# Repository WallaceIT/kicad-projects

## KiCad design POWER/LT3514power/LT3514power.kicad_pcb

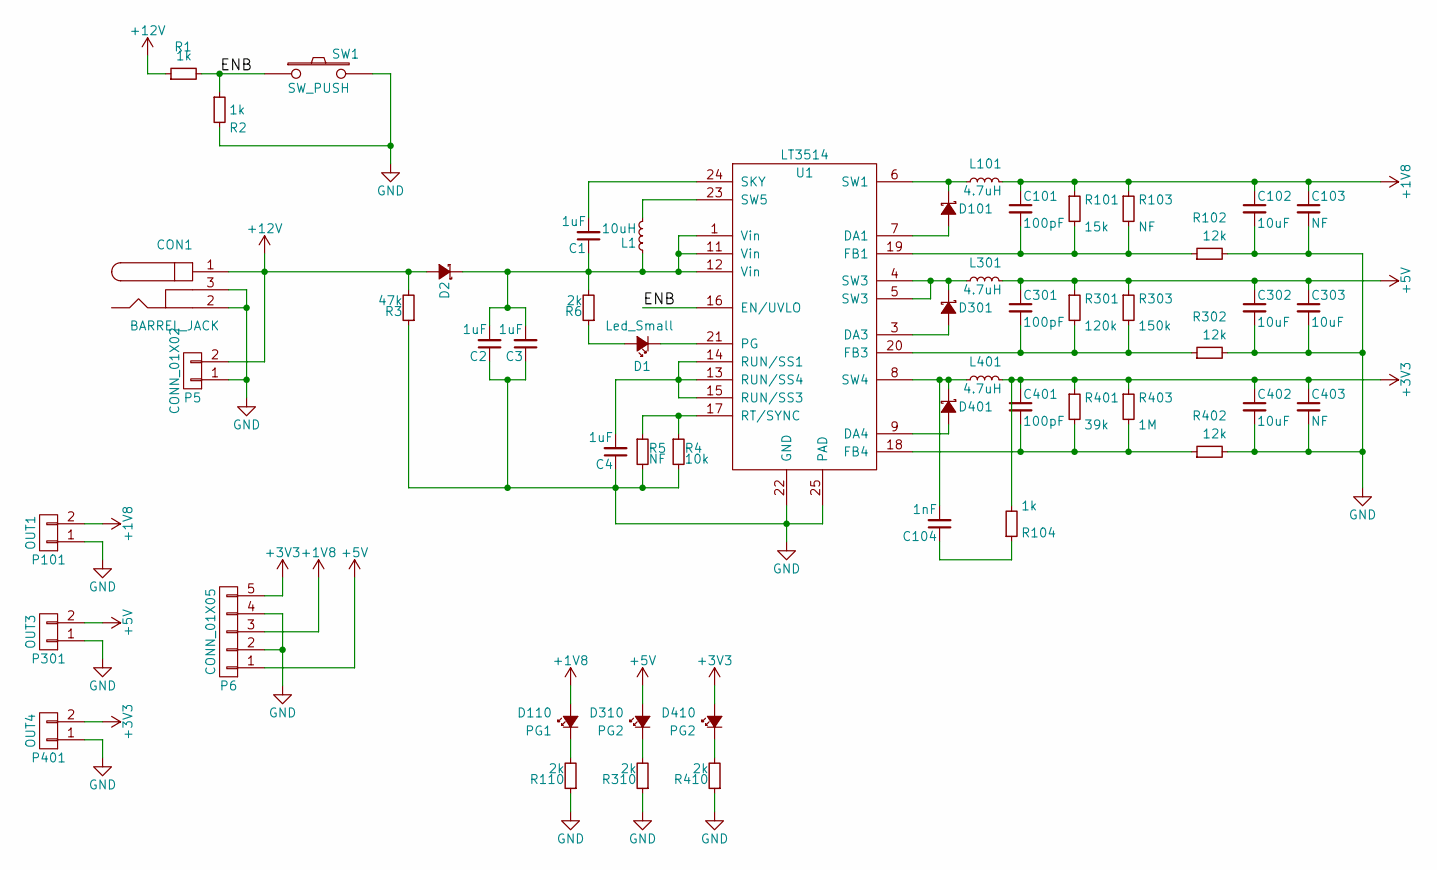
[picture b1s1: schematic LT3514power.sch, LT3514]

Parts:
C1, C2, C3, C4: 1uF; C_0805
C101, C301, C401: 100pF; C_0805
C102, C302, C303, C402: 10uF; C_0805
C103, C403: NF; C_0805
C104: 1nF; C_0805
CON1: BARREL_JACK
D1: Led_Small; LED_0805
D2, D101, D301, D401: D_Schottky_Small; DO-214AB
D110: PG1; LED_0805
D310, D410: PG2; LED_0805
L1: 10uH; EPL3015
L101, L301, L401: 4.7uH; MSS6132
P5: CONN_01X02; bornier2
P6: CONN_01X05; bornier5
P101: OUT1; Pin_Header_Straight_1x02
P301: OUT3; Pin_Header_Straight_1x02
P401: OUT4; Pin_Header_Straight_1x02
R1, R2, R104: 1k; R_0805
R3: 47k; R_0805
R4: 10k; R_0805
R5, R103: NF; R_0805
R6, R110, R310, R410: 2k; R_0805
R101: 15k; R_0805
R102, R302, R402: 12k; R_0805
R301: 120k; R_0805
R303: 150k; R_0805
R401: 39k; R_0805
R403: 1M; R_0805
SW1: SW_PUSH; SW_SPST_EVPBF
U1: LT3514; TSSOP-24_4.4x7.8mm_Pitch0.65mm

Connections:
+1V8: C101.1, C102.1, C103.1, D110.2 (A), L101.2, P6.3, P101.2, R101.1, R103.1
+3V3: C401.1, C402.1, C403.1, D410.2 (A), L401.2, P6.5, P401.2, R104.2, R401.1, R403.1
+5V: C301.1, C302.1, C303.1, D310.2 (A), L301.2, P6.1, P301.2, R301.1, R303.1
+12V: CON1.1, D2.2 (A), P5.2, R1.1, R3.2
/ENB: R1.2, R2.1, SW1.1, U1.16 (EN/UVLO)
GND: C2.1, C3.1, C4.1, C102.2, C103.2, C302.2, C303.2, C402.2, C403.2, CON1.2, CON1.3, P5.1, P6.2, P6.4, P101.1, P301.1, P401.1, R2.2, R3.1, R4.2, R5.2, R102.2, R110.1, R302.2, R310.1, R402.2, R410.1, SW1.2, U1.22 (GND), U1.25 (PAD)
unnamed: C1.1, C2.2, C3.2, D2.1 (K), L1.1, R6.2, U1.1 (Vin), U1.11 (Vin), U1.12 (Vin)
unnamed: C1.2, U1.24 (SKY)
unnamed: C4.2, U1.13 (RUN/SS4), U1.14 (RUN/SS1), U1.15 (RUN/SS3)
unnamed: C101.2, R101.2, R102.1, R103.2, U1.19 (FB1)
unnamed: C104.1, R104.1
unnamed: C104.2, D401.1 (K), L401.1, U1.8 (SW4)
unnamed: C301.2, R301.2, R302.1, R303.2, U1.20 (FB3)
unnamed: C401.2, R401.2, R402.1, R403.2, U1.18 (FB4)
unnamed: D1.1 (K), U1.21 (PG)
unnamed: D1.2 (A), R6.1
unnamed: D101.1 (K), L101.1, U1.6 (SW1)
unnamed: D101.2 (A), U1.7 (DA1)
unnamed: D110.1 (K), R110.2
unnamed: D301.1 (K), L301.1, U1.4 (SW3), U1.5 (SW3)
unnamed: D301.2 (A), U1.3 (DA3)
unnamed: D310.1 (K), R310.2
unnamed: D401.2 (A), U1.9 (DA4)
unnamed: D410.1 (K), R410.2
unnamed: L1.2, U1.23 (SW5)
unnamed: R4.1, R5.1, U1.17 (RT/SYNC)

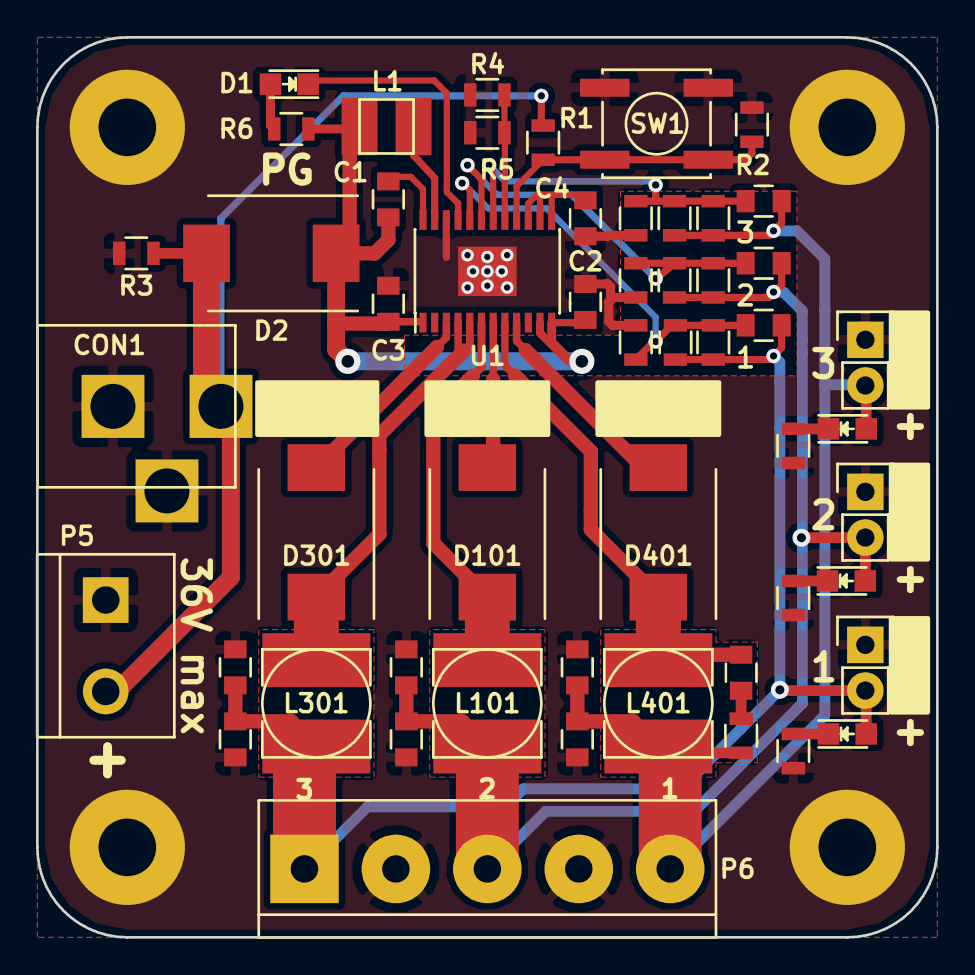
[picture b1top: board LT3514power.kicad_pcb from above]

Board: 2 copper layers, 50.0 x 50.0 mm, 53 parts (0 on the bottom side), 26 nets.

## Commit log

2016-07-28 LT3514power
